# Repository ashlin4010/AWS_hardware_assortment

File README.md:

# AWS Hardware Assortment
This is a assortment of pcbs made for a Convergent Technologies AWS.
These designs may contain faults or errors that could destroy or damage the themselves or the AWS.
USE AT YOUR OWN RISK

## Bill of Materials
At this stage I have not create a bill of materials, if and when I make updates  to the designs I will try to improve the documentation.

## USB To AWS Cluster Interface
The AWS communicates with two differential pairs, one for clock and one for data.
This board uses the
[Adafruit FT232H Breakout](https://www.adafruit.com/product/2264) combined with differential drivers/receivers to communicate with the cluster network.
It includes some leds controllable from the FT232H and overvoltage protection via a zener.
Note: This adaptor unlike the AWS is not able to transmit and receive to its self.

## CPU Interface Board
This is effectively a breakout board that allows an Turbo CPU board to interface with peripheralsand and receive power
inplace of the original AWS motherboard. It has the following functions: cluster connectors, keyboard connector,
speaker breakout and volume, power LED, reset button and LED, video interface connector, and power input.

## Composite Adapter (Untested)

The Composite Adapter is an attempts to convert the AWSs ttl video to composite. The adapter has been built to be modular,
one part contains a power supply circuit and differential line receiver.
The other part contains the circuitry that produces the sync signal and is responsible for combining everything into composite.
At this stage this adapter has not been testred and most of the resistor values are guesses hence the potentiometers.
Note: In order to create an NTSC compatible signal the AWS horizontal scan frequency needs to be decreased. This can be done via an external
clock at the J3 connector or Video Debug PCB (Pixel Clock of 14.1606MHz ≈ 15.734kHz horizontal scan).

## Video Debug Borad
The Video Debug Borad has to functions, provieds an external video clock and LED indicators for the character ROM.
The Video Debug Board is able to provide a small amount of insight into what the CRT controller is doing.
But for the most part is more decorative than functional.

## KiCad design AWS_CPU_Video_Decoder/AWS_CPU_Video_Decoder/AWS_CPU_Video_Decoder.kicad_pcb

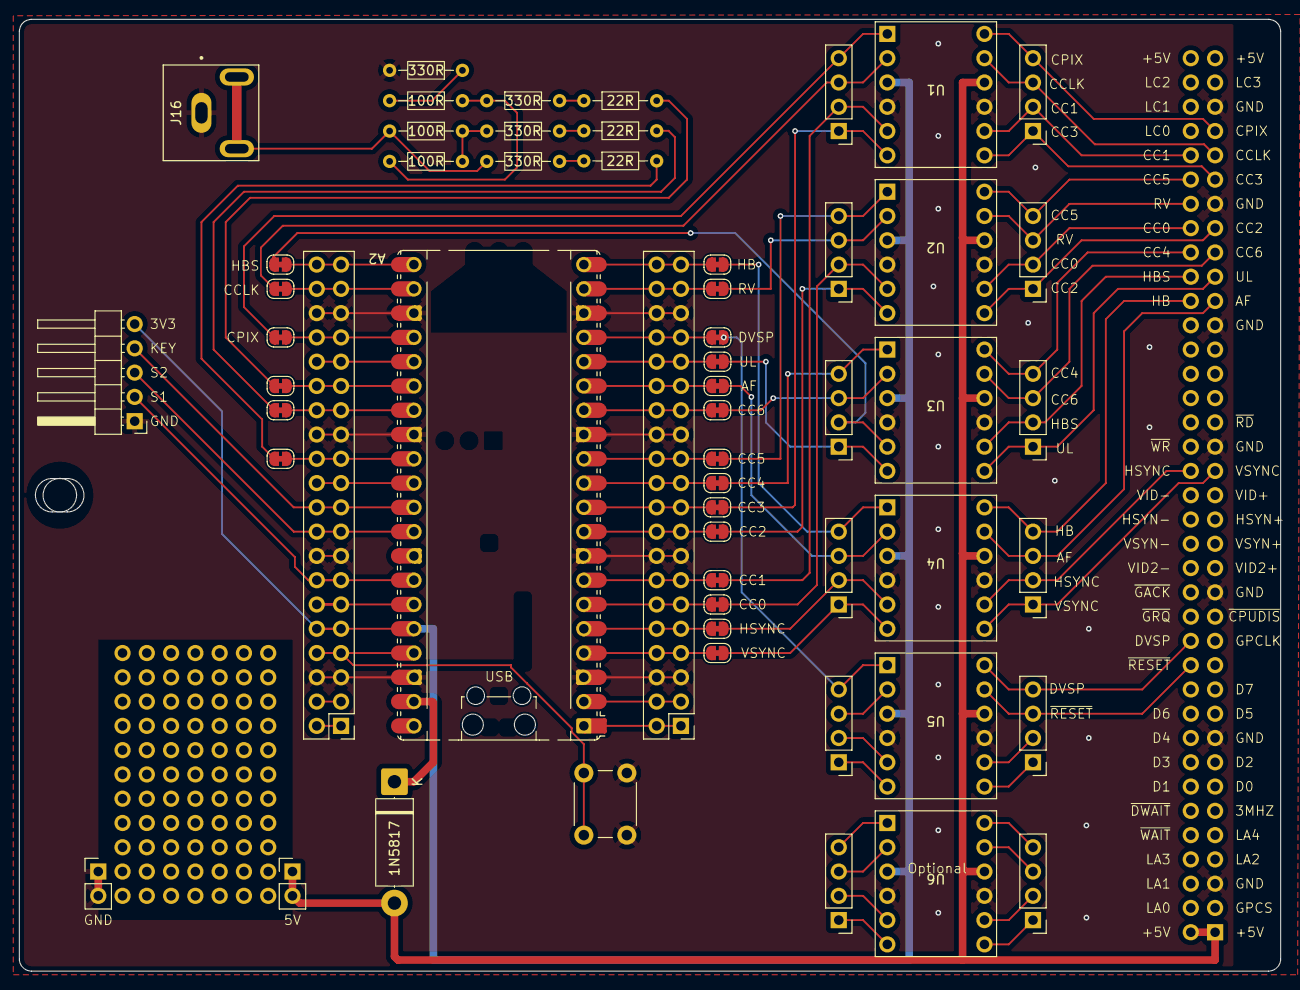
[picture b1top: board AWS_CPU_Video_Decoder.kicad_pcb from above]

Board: 2 copper layers, 132.0 x 99.6 mm, 59 parts (1 on the bottom side), 79 nets.

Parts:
A2: RaspberryPi_Pico; RaspberryPi_Pico_Common_Unspecified
D1: 1N5817; D_5W_P12.70mm_Horizontal
H1: MountingHole; MountingHole_3.5mm
J1, J5: Conn_02x20_Odd_Even; PinHeader_2x20_P2.54mm_Vertical
J2, J4, J6, J7, J8, J9, J10, J11, J12, J13, J14, J15: Conn_01x04_Pin; PinHeader_1x04_P2.54mm_Vertical
J3: Video; PinSocket_2x37_P2.54mm_Vertical
J16: Video; SWITCHCRAFT_PJRAN1X1U04X
J18, J19: Conn_01x02_Pin; PinHeader_1x02_P2.54mm_Vertical
J20: Encoder; PinHeader_1x05_P2.54mm_Horizontal
JP1, JP2, JP3, JP4, JP5, JP6, JP7, JP8, JP9, JP10, JP11, JP12, JP13, JP14, JP15, JP16, JP17, JP19, JP20, JP21: Jumper_2_Small_Bridged; SolderJumper-2_P1.3mm_Bridged_RoundedPad1.0x1.5mm
R1, R2, R3: 22R; R_Axial_DIN0204_L3.6mm_D1.6mm_P7.62mm_Horizontal
R4, R5, R6, R10: 330R; R_Axial_DIN0204_L3.6mm_D1.6mm_P7.62mm_Horizontal
R7, R8, R9: 100R; R_Axial_DIN0204_L3.6mm_D1.6mm_P7.62mm_Horizontal
SW1: Reset; SW_PUSH_6mm
U1, U2, U3, U4, U5, U6: level_shifter

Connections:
+3V3: A2.36 (3V3), J1.9, J1.10, J20.5, U1.3 (LV), U2.3 (LV), U3.3 (LV), U4.3 (LV), U5.3 (LV), U6.3 (LV)
+5V: D1.2 (A), J3.1, J3.2, J18.1, J18.2, U1.10 (HV), U2.10 (HV), U3.10 (HV), U4.10 (HV), U5.10 (HV), U6.10 (HV)
AF: J3.53, J15.3, U4.11 (HV2)
AF_LV: J7.3, JP10.1 (A), U4.2 (LV2)
CC0: J3.60, J12.2, U2.8 (HV3)
CC0_LV: J4.2, JP3.1 (A), U2.5 (LV3)
CC1: J3.66, J10.2, U1.8 (HV3)
CC1_LV: J2.2, JP4.1 (A), U1.5 (LV3)
CC2: J3.59, J12.1, U2.7 (HV4)
CC2_LV: J4.1, JP5.1 (A), U2.6 (LV4)
CC3: J3.63, J10.1, U1.7 (HV4)
CC3_LV: J2.1, JP6.1 (A), U1.6 (LV4)
CC4: J3.58, J14.4, U3.12 (HV1)
CC4_LV: J6.4, JP7.1 (A), U3.1 (LV1)
CC5: J3.64, J12.4, U2.12 (HV1)
CC5_LV: J4.4, JP8.1 (A), U2.1 (LV1)
CC6: J3.57, J14.3, U3.11 (HV2)
CC6_LV: J6.3, JP9.1 (A), U3.2 (LV2)
CCLK: J3.65, J10.3, U1.11 (HV2)
CCLK_LV: J2.3, JP15.2 (B), U1.2 (LV2)
CPIX: J3.67, J10.4, U1.12 (HV1)
CPIX_LV: J2.4, JP17.2 (B), U1.1 (LV1)
DAC0: A2.26 (GPIO20), J1.29, J1.30, JP21.2 (B)
DAC1: A2.27 (GPIO21), J1.27, J1.28, JP20.2 (B)
DAC2: A2.29 (GPIO22), J1.23, J1.24, JP19.2 (B)
DVSP: J3.26, J13.4, U5.12 (HV1)
DVSP_LV: J8.4, JP12.1 (A), U5.1 (LV1)
GND: A2.3 (GND), A2.8 (GND), A2.13 (GND), A2.18 (GND), A2.23 (GND), A2.28 (GND), A2.38 (GND), J1.5, J1.6, J1.15, J1.16, J1.25, J1.26, J1.35, J1.36, J3.5, J3.17, J3.29, J3.41, J3.51, J3.61, J3.69, J5.5, J5.6, J5.15, J5.16, J5.25, J5.26, J5.35, J5.36, J16.2 (Ext), J19.1, J19.2, J20.1, R10.2, SW1.2, U1.4 (GND), U1.9 (GND), U2.4 (GND), U2.9 (GND), U3.4 (GND), U3.9 (GND), U4.4 (GND), U4.9 (GND), U5.4 (GND), U5.9 (GND), U6.4 (GND), U6.9 (GND)
GPIO0: A2.1 (GPIO0), J5.1, J5.2
GPIO1: A2.2 (GPIO1), J5.3, J5.4
GPIO2: A2.4 (GPIO2), J5.7, J5.8, JP1.2 (B)
GPIO3: A2.5 (GPIO3), J5.9, J5.10, JP2.2 (B)
GPIO4: A2.6 (GPIO4), J5.11, J5.12, JP3.2 (B)
GPIO5: A2.7 (GPIO5), J5.13, J5.14, JP4.2 (B)
GPIO6: A2.9 (GPIO6), J5.17, J5.18, JP5.2 (B)
GPIO7: A2.10 (GPIO7), J5.19, J5.20, JP6.2 (B)
GPIO8: A2.11 (GPIO8), J5.21, J5.22, JP7.2 (B)
GPIO9: A2.12 (GPIO9), J5.23, J5.24, JP8.2 (B)
GPIO10: A2.14 (GPIO10), J5.27, J5.28, JP9.2 (B)
GPIO11: A2.15 (GPIO11), J5.29, J5.30, JP10.2 (B)
GPIO12: A2.16 (GPIO12), J5.31, J5.32, JP11.2 (B)
GPIO13: A2.17 (GPIO13), J5.33, J5.34, JP12.2 (B)
GPIO14: A2.19 (GPIO14), J5.37, J5.38, JP13.2 (B)
GPIO15: A2.20 (GPIO15), J5.39, J5.40, JP14.2 (B)
GPIO16: A2.21 (GPIO16), J1.39, J1.40, JP16.1 (A)
GPIO17: A2.22 (GPIO17), J1.37, J1.38, JP15.1 (A)
GPIO18: A2.24 (GPIO18), J1.33, J1.34, JP17.1 (A)
GPIO19: A2.25 (GPIO19), J1.31, J1.32
GPIO26: A2.31 (GPIO26_ADC0), J1.19, J1.20, J20.4
GPIO27: A2.32 (GPIO27_ADC1), J1.17, J1.18, J20.3
GPIO28: A2.34 (GPIO28_ADC2), J1.13, J1.14, J20.2
HB: J3.54, J15.4, U4.12 (HV1)
HBS: J3.56, J14.2, U3.8 (HV3)
HBS_LV: J6.2, JP16.2 (B), U3.5 (LV3)
HB_LV: J7.4, JP14.1 (A), U4.1 (LV1)
HSYNC: J3.40, J15.2, U4.8 (HV3)
HSYNC_LV: J7.2, JP2.1 (A), U4.5 (LV3)
unnamed: A2.39 (VSYS), D1.1 (K)
unnamed: J16.1 (In), R6.1, R8.1
unnamed: JP19.1 (A), R3.2
unnamed: JP20.1 (A), R2.2
unnamed: JP21.1 (A), R1.2
unnamed: R1.1, R4.2
unnamed: R2.1, R5.2
unnamed: R3.1, R6.2
unnamed: R4.1, R7.1, R9.2
unnamed: R5.1, R8.2, R9.1
unnamed: R7.2, R10.1
P_RESET: A2.37 (3V3_EN), J1.7, J1.8, SW1.1
RUN: A2.30 (RUN), J1.21, J1.22
RV: J3.62, J12.3, U2.11 (HV2)
RV_LV: J4.3, JP13.1 (A), U2.2 (LV2)
UL: J3.55, J14.1, U3.7 (HV4)
UL_LV: J6.1, JP11.1 (A), U3.6 (LV4)
VREF: A2.35 (ADC_VREF), J1.11, J1.12
VSYNC: J3.39, J15.1, U4.7 (HV4)
VSYNC_LV: J7.1, JP1.1 (A), U4.6 (LV4)
~RESET_LV: J8.3, U5.2 (LV2)
~RESET: J3.24, J13.3, U5.11 (HV2)

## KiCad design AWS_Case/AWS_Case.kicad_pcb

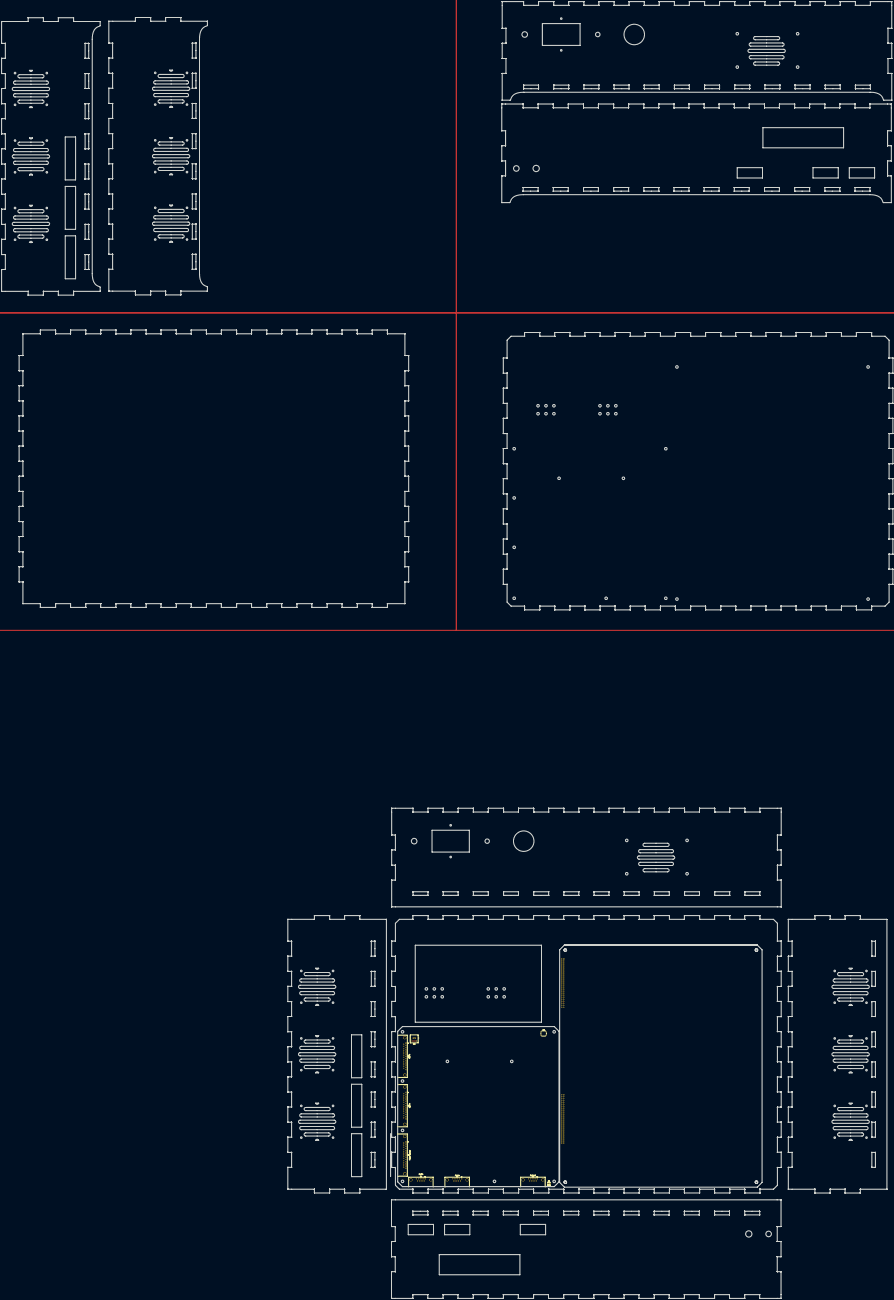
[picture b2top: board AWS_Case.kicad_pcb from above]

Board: 2 copper layers, 1122.7 x 1633.6 mm, 9 parts (0 on the bottom side), 6 nets, no tracks yet.

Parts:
D1: Power; LED_D3.0mm
J3, J4: Cluster; DSUB-9_Socket_Horizontal_P2.77x2.84mm_EdgePinOffset7.70mm_H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
J7: Keyboard; DSUB-9_Socket_Horizontal_P2.77x2.84mm_EdgePinOffset7.70mm_H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
J8: Printer Interface; DSUB-25_Pins_Horizontal_P2.77x2.84mm_EdgePinOffset7.70mm_Ho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
J9: UART A; DSUB-25_Pins_Horizontal_P2.77x2.84mm_EdgePinOffset7.70mm_Ho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
J10: UART B; DSUB-25_Pins_Horizontal_P2.77x2.84mm_EdgePinOffset7.70mm_Ho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
J12: Video; SWITCHCRAFT_PJRAN1X1U04X
SW1: Reset; SW_PUSH_6mm

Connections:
+5V: J7.6, J7.7
CPU_RXCA+: J3.6, J4.6
CPU_RXCA-: J3.7, J4.7
CPU_RXDA+: J3.8, J4.8
CPU_RXDA-: J3.9, J4.9
GND: D1.1 (K), J3.1, J3.2, J3.3, J3.4, J3.5, J4.1, J4.2, J4.3, J4.4, J4.5, J7.2, J7.4, J7.8, J7.9, J8.9, J8.10, J8.11, J8.12, J8.13, J8.15, J8.23, J8.24, J8.25, J9.1, J9.7, J9.9, J10.1, J10.7, J10.9, J12.2 (Ext), SW1.2

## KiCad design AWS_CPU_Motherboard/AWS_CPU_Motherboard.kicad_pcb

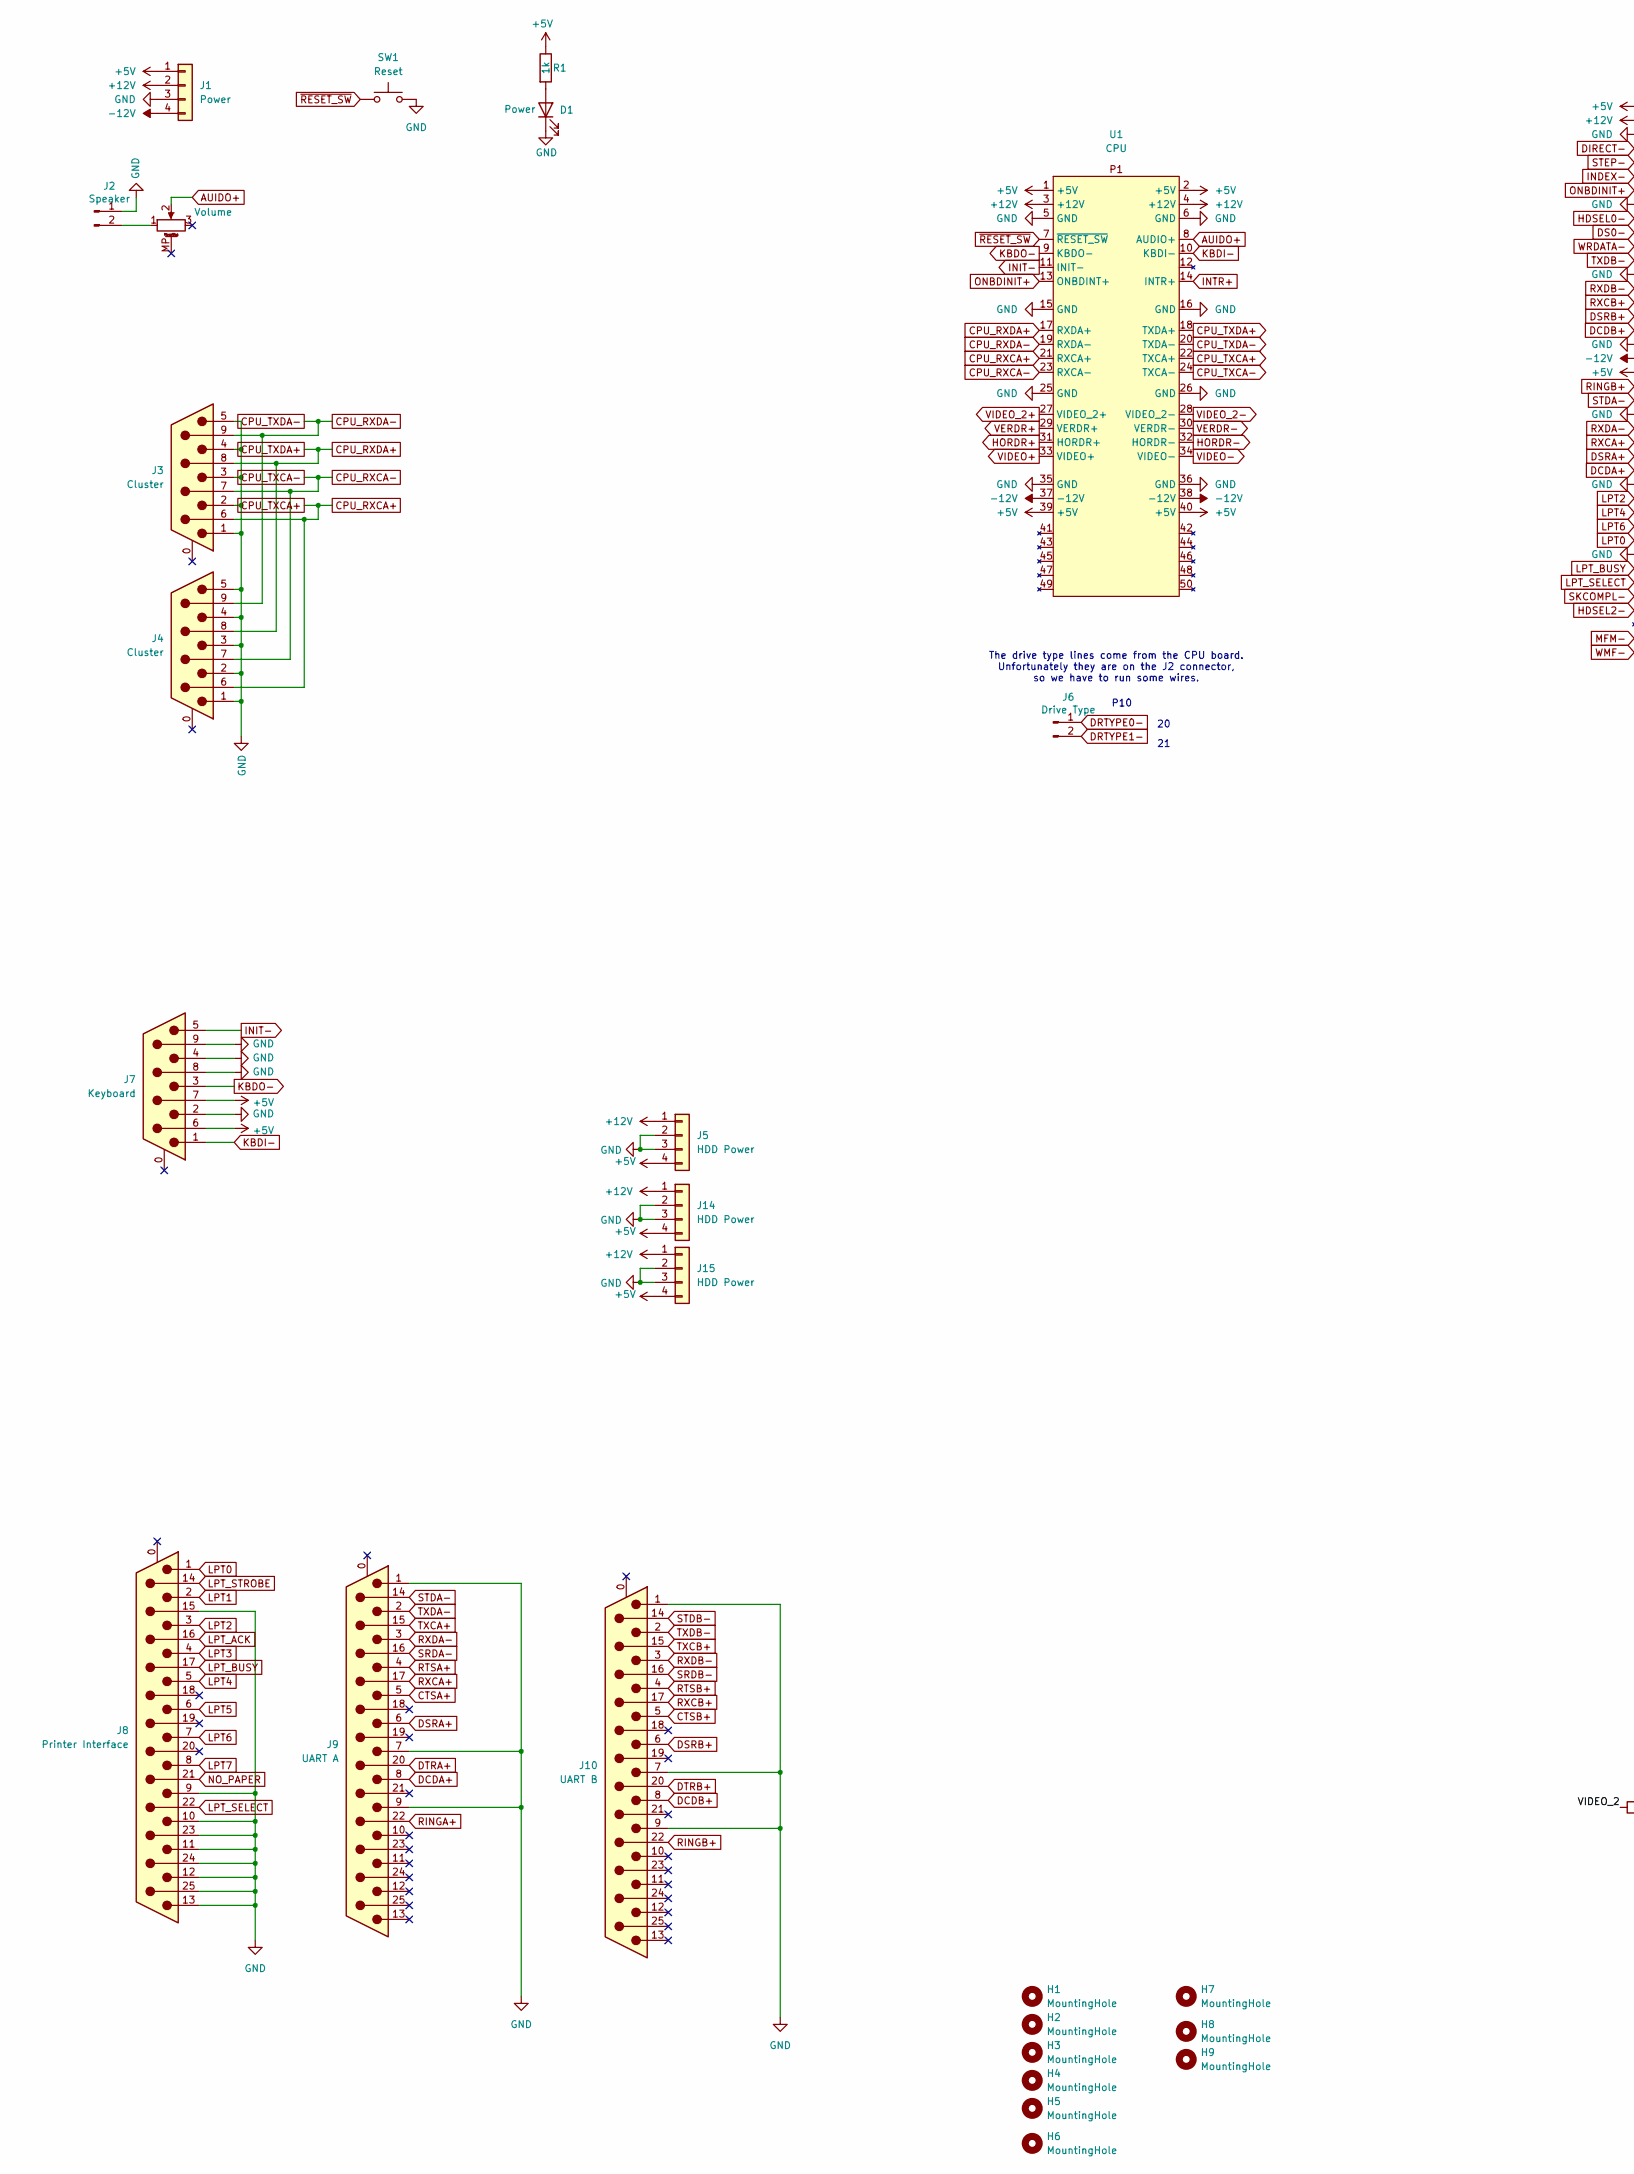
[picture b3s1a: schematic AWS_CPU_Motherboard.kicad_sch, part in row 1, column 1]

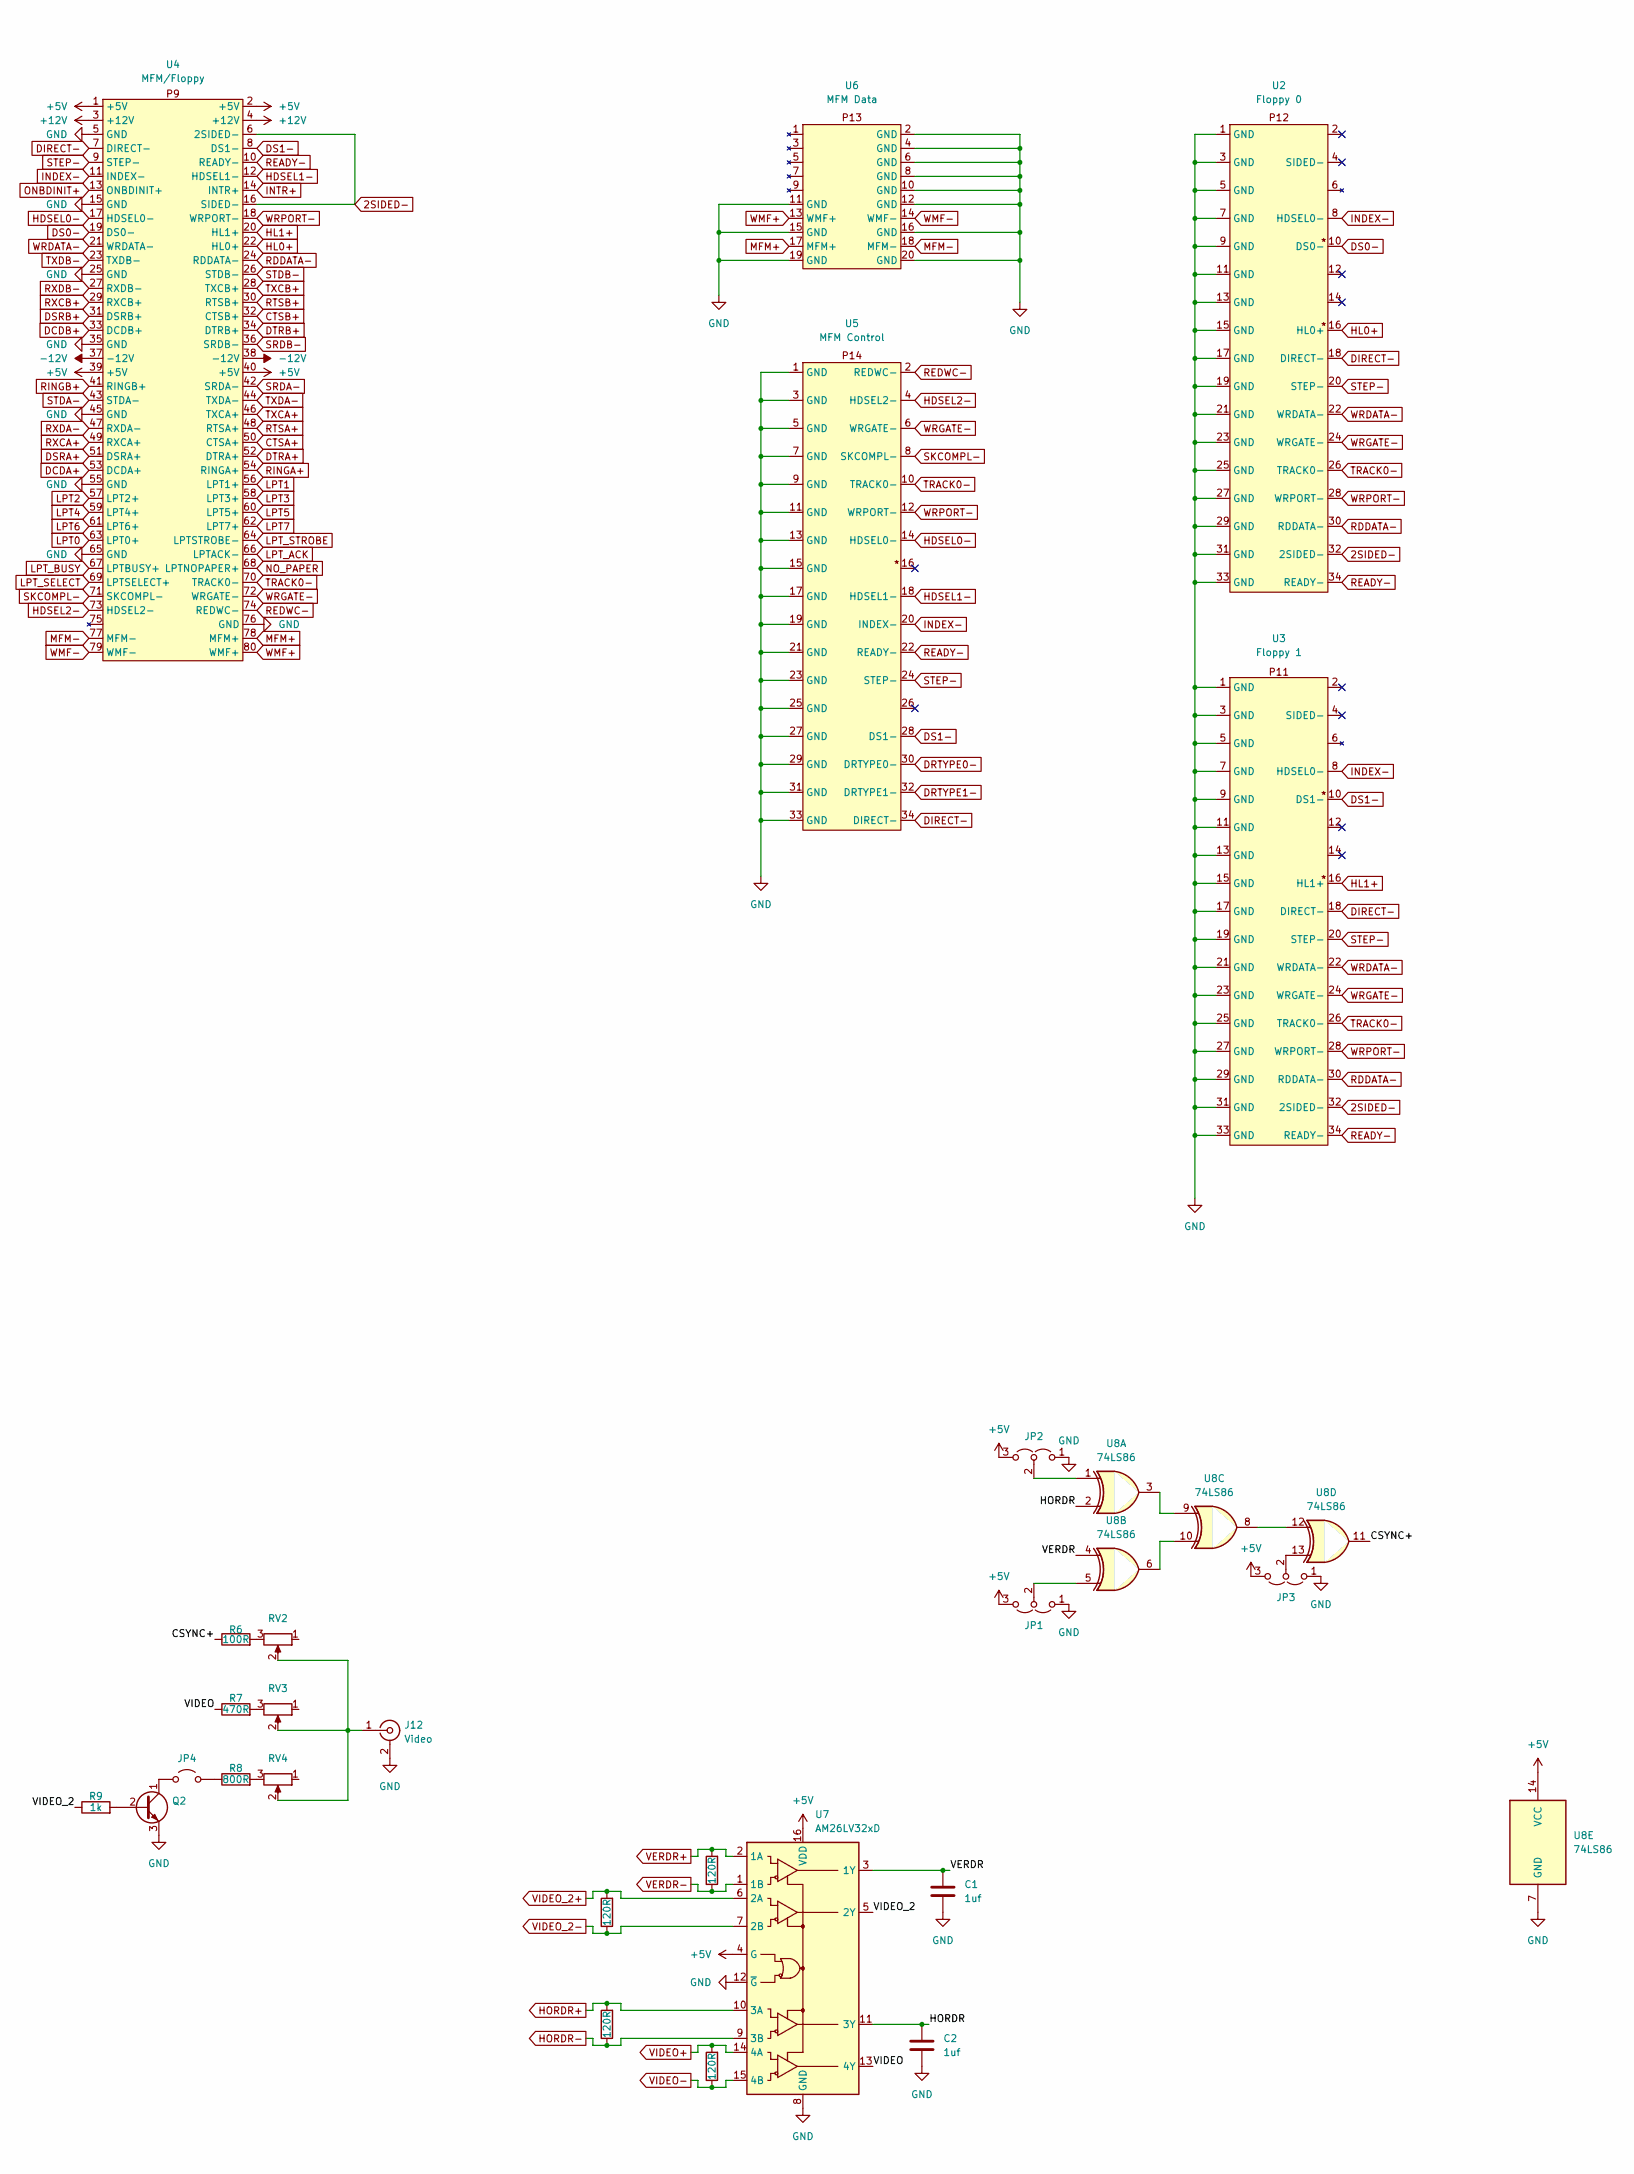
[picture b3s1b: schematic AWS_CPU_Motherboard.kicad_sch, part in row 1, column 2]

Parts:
C1, C2: 1uf; C_Disc_D3.0mm_W1.6mm_P2.50mm
D1: Power; LED_D3.0mm
H1, H2, H3, H4, H5, H6, H7, H8, H9: MountingHole; MountingHole_3.2mm_M3
J1: Power; TerminalBlock_Dinkle_DT-55-B01X-04_P10.00mm
J2: Speaker; PinHeader_1x02_P2.54mm_Vertical
J3, J4: Cluster; DSUB-9_Socket_Horizontal_P2.77x2.84mm_EdgePinOffset7.70mm_H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
J5, J14, J15: HDD Power; TE_MATE-N-LOK_350211-1_1x04_P5.08mm_Vertical
J6: Drive Type; PinHeader_1x02_P2.54mm_Vertical
J7: Keyboard; DSUB-9_Socket_Horizontal_P2.77x2.84mm_EdgePinOffset7.70mm_H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
J8: Printer Interface; DSUB-25_Pins_Horizontal_P2.77x2.84mm_EdgePinOffset7.70mm_Ho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
J9: UART A; DSUB-25_Pins_Horizontal_P2.77x2.84mm_EdgePinOffset7.70mm_Ho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
J10: UART B; DSUB-25_Pins_Horizontal_P2.77x2.84mm_EdgePinOffset7.70mm_Ho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
J12: Video; SWITCHCRAFT_PJRAN1X1U04X
JP1, JP2, JP3: Jumper_3_Open; PinHeader_1x03_P2.54mm_Vertical
JP4: Enable Half Bright; PinHeader_1x02_P2.54mm_Vertical
Q2: Q_NPN_CBE; TO-92
R1, R9: 1k; R_Axial_DIN0204_L3.6mm_D1.6mm_P7.62mm_Horizontal
R2, R3, R4, R5: 120R; R_Axial_DIN0204_L3.6mm_D1.6mm_P7.62mm_Horizontal
R6: 100R; R_Axial_DIN0204_L3.6mm_D1.6mm_P7.62mm_Horizontal
R7: 470R; R_Axial_DIN0204_L3.6mm_D1.6mm_P7.62mm_Horizontal
R8: 800R; R_Axial_DIN0204_L3.6mm_D1.6mm_P7.62mm_Horizontal
RV1: Volume; Potentiometer_Bourns_PTV09A-1_Single_Vertical
RV2: CSYNC+; Potentiometer_Piher_PT-10-V10_Vertical
RV3: VIDEO; Potentiometer_Piher_PT-10-V10_Vertical
RV4: Half; Potentiometer_Piher_PT-10-V10_Vertical
SW1: Reset; SW_PUSH_6mm
U1: CPU; IDC-Header_2x25_P2.54mm_Vertical_Reversed
U2: Floppy 0; IDC-Header_2x17_P2.54mm_Vertical
U3: Floppy 1; IDC-Header_2x17_P2.54mm_Vertical
U4: MFM/Floppy; PinHeader_2x40_P2.54mm_Horizontal_Reversed
U5: MFM Control; IDC-Header_2x17_P2.54mm_Vertical
U6: MFM Data; IDC-Header_2x10_P2.54mm_Vertical
U7: AM26LV32xD; DIP-16_W7.62mm_LongPads
U8: 74LS86; DIP-14_W7.62mm_LongPads

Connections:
2SIDED-: U2.32 (2SIDED-), U3.32 (2SIDED-), U4.6 (2SIDED-), U4.16 (SIDED-)
+5V: J1.1, J5.4, J7.6, J7.7, J14.4, J15.4, JP1.3 (B), JP2.3 (B), JP3.3 (B), R1.1, U1.1 (+5V), U1.2 (+5V), U1.39 (+5V), U1.40 (+5V), U4.1 (+5V), U4.2 (+5V), U4.39 (+5V), U4.40 (+5V), U7.4 (G), U7.16 (VDD), U8.14 (VCC)
+12V: J1.2, J5.1, J14.1, J15.1, U1.3 (+12V), U1.4 (+12V), U4.3 (+12V), U4.4 (+12V)
-12V: J1.4, U1.37 (-12V), U1.38 (-12V), U4.37 (-12V), U4.38 (-12V)
/CSYNC+: R6.1, U8.11
/HORDR: C2.1, U7.11 (3Y), U8.2
/VERDR: C1.1, U7.3 (1Y), U8.4
/VIDEO: R7.1, U7.13 (4Y)
/VIDEO_2: R9.1, U7.5 (2Y)
AUIDO+: RV1.2, U1.8 (AUDIO+)
CPU_RXCA+: J3.6, J4.6, U1.21 (RXCA+), U1.22 (TXCA+)
CPU_RXCA-: J3.7, J4.7, U1.23 (RXCA-), U1.24 (TXCA-)
CPU_RXDA+: J3.8, J4.8, U1.17 (RXDA+), U1.18 (TXDA+)
CPU_RXDA-: J3.9, J4.9, U1.19 (RXDA-), U1.20 (TXDA-)
CTSA+: J9.5, U4.50 (CTSA+)
CTSB+: J10.5, U4.32 (CTSB+)
DCDA+: J9.8, U4.53 (DCDA+)
DCDB+: J10.8, U4.33 (DCDB+)
DIRECT-: U2.18 (DIRECT-), U3.18 (DIRECT-), U4.7 (DIRECT-), U5.34 (DIRECT-)
DRTYPE0-: J6.1, U5.30 (DRTYPE0-)
DRTYPE1-: J6.2, U5.32 (DRTYPE1-)
DS0-: U2.10 (DS0-), U4.19 (DS0-)
DS1-: U3.10 (DS1-), U4.8 (DS1-), U5.28 (DS1-)
DSRA+: J9.6, U4.51 (DSRA+)
DSRB+: J10.6, U4.31 (DSRB+)
DTRA+: J9.20, U4.52 (DTRA+)
DTRB+: J10.20, U4.34 (DTRB+)
GND: C1.2, C2.2, D1.1 (K), J1.3, J2.1, J3.1, J3.2, J3.3, J3.4, J3.5, J4.1, J4.2, J4.3, J4.4, J4.5, J5.2, J5.3, J7.2, J7.4, J7.8, J7.9, J8.9, J8.10, J8.11, J8.12, J8.13, J8.15, J8.23, J8.24, J8.25, J9.1, J9.7, J9.9, J10.1, J10.7, J10.9, J12.2 (Ext), J14.2, J14.3, J15.2, J15.3, JP1.1 (A), JP2.1 (A), JP3.1 (A), Q2.3 (E), SW1.2, U1.5 (GND), U1.6 (GND), U1.15 (GND), U1.16 (GND), U1.25 (GND), U1.26 (GND), U1.35 (GND), U1.36 (GND), U2.1 (GND), U2.3 (GND), U2.5 (GND), U2.7 (GND), U2.9 (GND), U2.11 (GND), U2.13 (GND), U2.15 (GND), U2.17 (GND), U2.19 (GND), U2.21 (GND), U2.23 (GND), U2.25 (GND), U2.27 (GND), U2.29 (GND), U2.31 (GND), U2.33 (GND), U3.1 (GND), U3.3 (GND), U3.5 (GND), U3.7 (GND), U3.9 (GND), U3.11 (GND), U3.13 (GND), U3.15 (GND), U3.17 (GND), U3.19 (GND), U3.21 (GND), U3.23 (GND), U3.25 (GND), U3.27 (GND), U3.29 (GND), U3.31 (GND), U3.33 (GND), U4.5 (GND), U4.15 (GND), U4.25 (GND), U4.35 (GND), U4.45 (GND), U4.55 (GND), U4.65 (GND), U4.76 (GND), U5.1 (GND), U5.3 (GND), U5.5 (GND), U5.7 (GND), U5.9 (GND), U5.11 (GND), U5.13 (GND), U5.15 (GND), U5.17 (GND), U5.19 (GND), U5.21 (GND), U5.23 (GND), U5.25 (GND), U5.27 (GND), U5.29 (GND), U5.31 (GND), U5.33 (GND), U6.2 (GND), U6.4 (GND), U6.6 (GND), U6.8 (GND), U6.10 (GND), U6.11 (GND), U6.12 (GND), U6.15 (GND), U6.16 (GND), U6.19 (GND), U6.20 (GND), U7.8 (GND), U7.12 (~G), U8.7 (GND)
HDSEL0-: U4.17 (HDSEL0-), U5.14 (HDSEL0-)
HDSEL1-: U4.12 (HDSEL1-), U5.18 (HDSEL1-)
HDSEL2-: U4.73 (HDSEL2-), U5.4 (HDSEL2-)
HL0+: U2.16 (HL0+), U4.22 (HL0+)
HL1+: U3.16 (HL1+), U4.20 (HL1+)
HORDR+: R5.2, U1.31 (HORDR+), U7.10 (3A)
HORDR-: R5.1, U1.32 (HORDR-), U7.9 (3B)
INDEX-: U2.8 (HDSEL0-), U3.8 (HDSEL0-), U4.11 (INDEX-), U5.20 (INDEX-)
INIT-: J7.5, U1.11 (INIT-)
INTR+: U1.14 (INTR+), U4.14 (INTR+)
KBDI-: J7.1, U1.10 (KBDI-)
KBDO-: J7.3, U1.9 (KBDO-)
LPT0: J8.1, U4.63 (LPT0+)
LPT1: J8.2, U4.56 (LPT1+)
LPT2: J8.3, U4.57 (LPT2+)
LPT3: J8.4, U4.58 (LPT3+)
LPT4: J8.5, U4.59 (LPT4+)
LPT5: J8.6, U4.60 (LPT5+)
LPT6: J8.7, U4.61 (LPT6+)
LPT7: J8.8, U4.62 (LPT7+)
LPT_ACK: J8.16, U4.66 (LPTACK-)
LPT_BUSY: J8.17, U4.67 (LPTBUSY+)
LPT_SELECT: J8.22, U4.69 (LPTSELECT+)
LPT_STROBE: J8.14, U4.64 (LPTSTROBE-)
MFM+: U4.78 (MFM+), U6.17 (MFM+)
MFM-: U4.77 (MFM-), U6.18 (MFM-)
NO_PAPER: J8.21, U4.68 (LPTNOPAPER+)
unnamed: D1.2 (A), R1.2
unnamed: J2.2, RV1.1
unnamed: J12.1 (In), RV2.2, RV3.2, RV4.2
unnamed: JP1.2 (C), U8.5
unnamed: JP2.2 (C), U8.1
unnamed: JP3.2 (C), U8.13
unnamed: JP4.1 (A), Q2.1 (C)
unnamed: JP4.2 (B), R8.1
unnamed: Q2.2 (B), R9.2
unnamed: R6.2, RV2.3
unnamed: R7.2, RV3.3
unnamed: R8.2, RV4.3
unnamed: U8.3, U8.9
unnamed: U8.6, U8.10
unnamed: U8.8, U8.12
ONBDINIT+: U1.13 (ONBDINT+), U4.13 (ONBDINIT+)
RDDATA-: U2.30 (RDDATA-), U3.30 (RDDATA-), U4.24 (RDDATA-)
READY-: U2.34 (READY-), U3.34 (READY-), U4.10 (READY-), U5.22 (READY-)
REDWC-: U4.74 (REDWC-), U5.2 (REDWC-)
RINGA+: J9.22, U4.54 (RINGA+)
RINGB+: J10.22, U4.41 (RINGB+)
RTSA+: J9.4, U4.48 (RTSA+)
RTSB+: J10.4, U4.30 (RTSB+)
RXCA+: J9.17, U4.49 (RXCA+)
RXCB+: J10.17, U4.29 (RXCB+)
RXDA-: J9.3, U4.47 (RXDA-)
RXDB-: J10.3, U4.27 (RXDB-)
SKCOMPL-: U4.71 (SKCOMPL-), U5.8 (SKCOMPL-)
SRDA-: J9.16, U4.42 (SRDA-)
SRDB-: J10.16, U4.36 (SRDB-)
STDA-: J9.14, U4.43 (STDA-)
STDB-: J10.14, U4.26 (STDB-)
STEP-: U2.20 (STEP-), U3.20 (STEP-), U4.9 (STEP-), U5.24 (STEP-)
TRACK0-: U2.26 (TRACK0-), U3.26 (TRACK0-), U4.70 (TRACK0-), U5.10 (TRACK0-)
TXCA+: J9.15, U4.46 (TXCA+)
TXCB+: J10.15, U4.28 (TXCB+)
TXDA-: J9.2, U4.44 (TXDA-)
TXDB-: J10.2, U4.23 (TXDB-)
VERDR+: R2.2, U1.29 (VERDR+), U7.2 (1A)
VERDR-: R2.1, U1.30 (VERDR-), U7.1 (1B)
VIDEO+: R3.2, U1.33 (VIDEO+), U7.14 (4A)
VIDEO-: R3.1, U1.34 (VIDEO-), U7.15 (4B)
VIDEO_2+: R4.2, U1.27 (VIDEO_2+), U7.6 (2A)
VIDEO_2-: R4.1, U1.28 (VIDEO_2-), U7.7 (2B)
WMF+: U4.80 (WMF+), U6.13 (WMF+)
WMF-: U4.79 (WMF-), U6.14 (WMF-)
WRDATA-: U2.22 (WRDATA-), U3.22 (WRDATA-), U4.21 (WRDATA-)
WRGATE-: U2.24 (WRGATE-), U3.24 (WRGATE-), U4.72 (WRGATE-), U5.6 (WRGATE-)
WRPORT-: U2.28 (WRPORT-), U3.28 (WRPORT-), U4.18 (WRPORT-), U5.12 (WRPORT-)
~RESET_SW: SW1.1, U1.7 (~RESET_SW)

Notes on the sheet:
The drive type lines come from the CPU board. Unfortunately they are on the J2 connector, so we have to run some wires.
P10

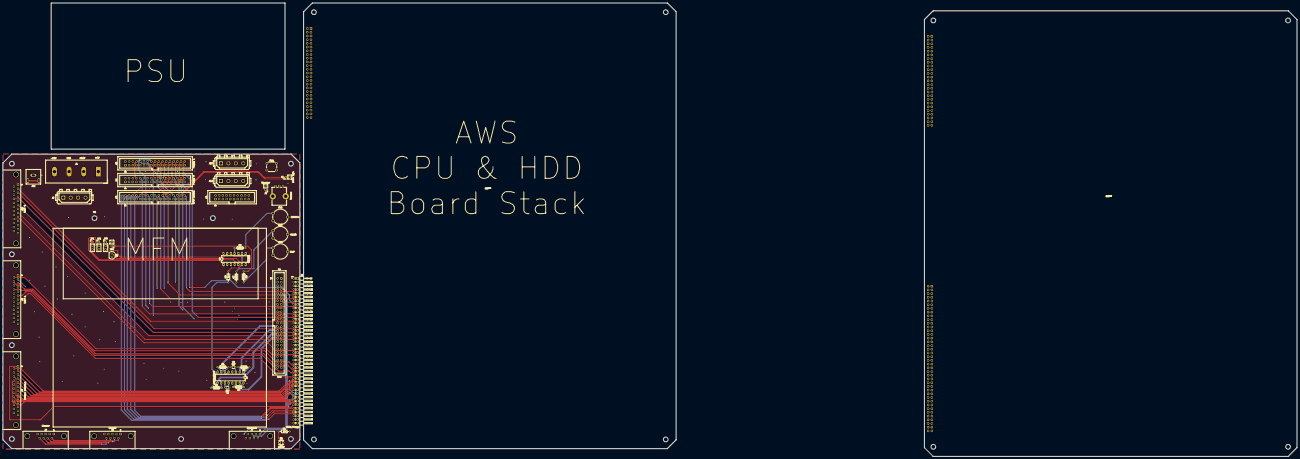
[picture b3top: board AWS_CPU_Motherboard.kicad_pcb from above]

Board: 4 copper layers, 885.7 x 310.3 mm, 52 parts (0 on the bottom side), 105 nets.

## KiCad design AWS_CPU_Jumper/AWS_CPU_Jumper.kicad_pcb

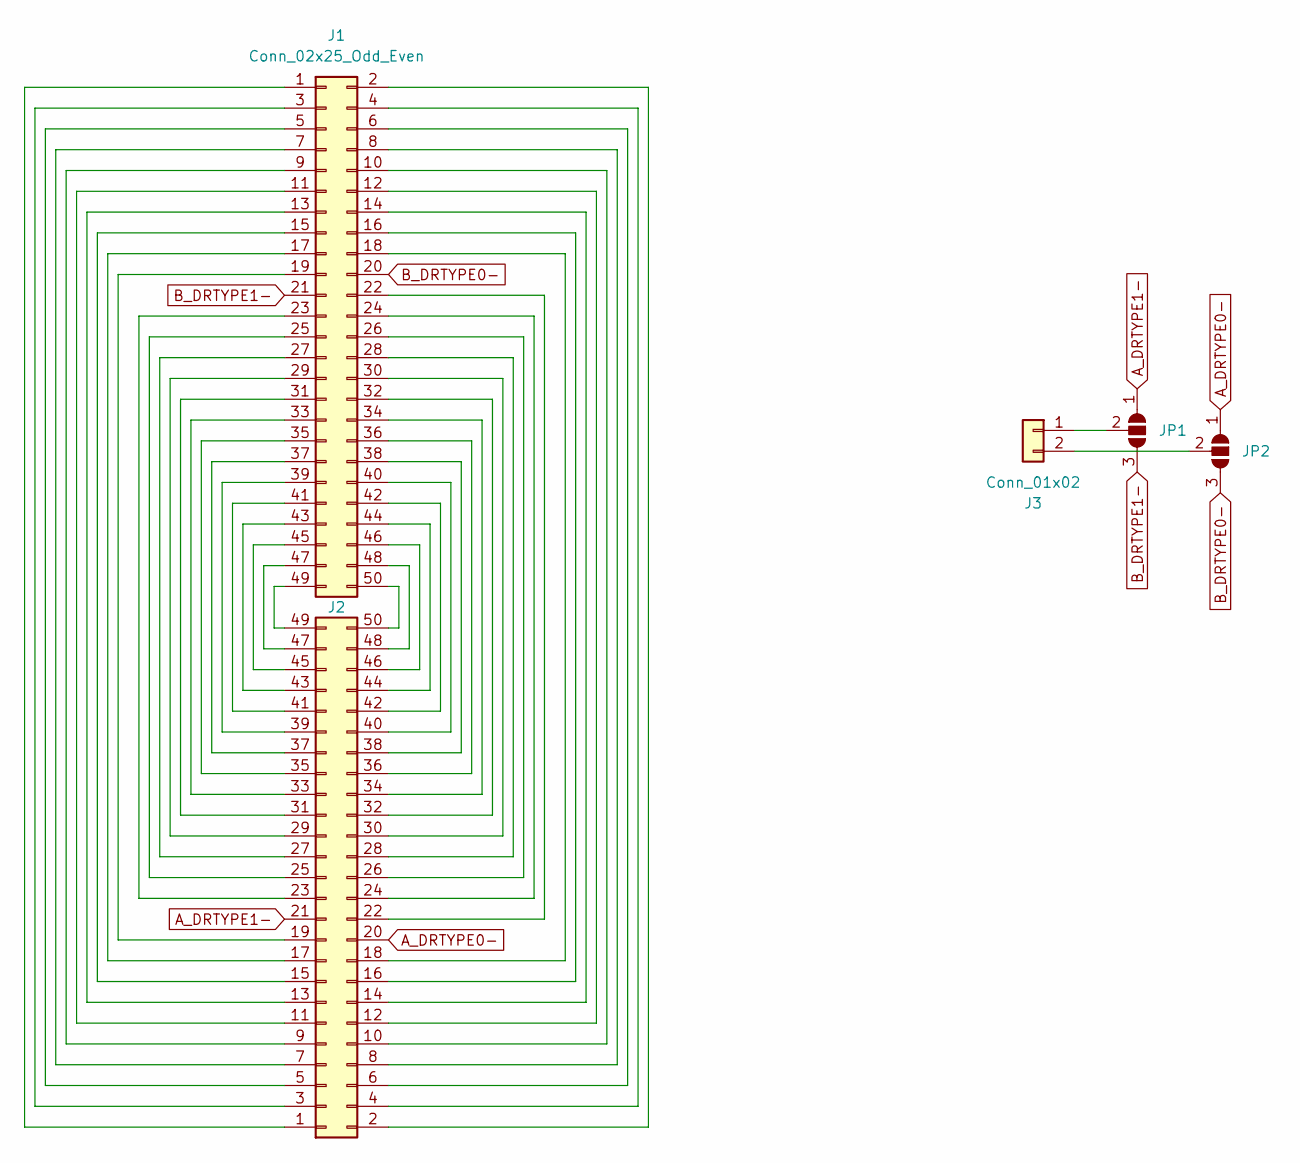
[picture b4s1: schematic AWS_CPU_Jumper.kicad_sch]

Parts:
J1, J2: Conn_02x25_Odd_Even; PinHeader_2x25_P2.54mm_Vertical
J3: Conn_01x02; PinHeader_1x02_P2.54mm_Vertical
JP1, JP2: SolderJumper_3_Open; SolderJumper-3_P1.3mm_Open_RoundedPad1.0x1.5mm

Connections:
A_DRTYPE0-: J2.20, JP2.1 (A)
A_DRTYPE1-: J2.21, JP1.1 (A)
B_DRTYPE0-: J1.20, JP2.3 (B)
B_DRTYPE1-: J1.21, JP1.3 (B)
unnamed: J1.1, J2.1
unnamed: J1.2, J2.2
unnamed: J1.3, J2.3
unnamed: J1.4, J2.4
unnamed: J1.5, J2.5
unnamed: J1.6, J2.6
unnamed: J1.7, J2.7
unnamed: J1.8, J2.8
unnamed: J1.9, J2.9
unnamed: J1.10, J2.10
unnamed: J1.11, J2.11
unnamed: J1.12, J2.12
unnamed: J1.13, J2.13
unnamed: J1.14, J2.14
unnamed: J1.15, J2.15
unnamed: J1.16, J2.16
unnamed: J1.17, J2.17
unnamed: J1.18, J2.18
unnamed: J1.19, J2.19
unnamed: J1.22, J2.22
unnamed: J1.23, J2.23
unnamed: J1.24, J2.24
unnamed: J1.25, J2.25
unnamed: J1.26, J2.26
unnamed: J1.27, J2.27
unnamed: J1.28, J2.28
unnamed: J1.29, J2.29
unnamed: J1.30, J2.30
unnamed: J1.31, J2.31
unnamed: J1.32, J2.32
unnamed: J1.33, J2.33
unnamed: J1.34, J2.34
unnamed: J1.35, J2.35
unnamed: J1.36, J2.36
unnamed: J1.37, J2.37
unnamed: J1.38, J2.38
unnamed: J1.39, J2.39
unnamed: J1.40, J2.40
unnamed: J1.41, J2.41
unnamed: J1.42, J2.42
unnamed: J1.43, J2.43
unnamed: J1.44, J2.44
unnamed: J1.45, J2.45
unnamed: J1.46, J2.46
unnamed: J1.47, J2.47
unnamed: J1.48, J2.48
unnamed: J1.49, J2.49
unnamed: J1.50, J2.50
unnamed: J3.1, JP1.2 (C)
unnamed: J3.2, JP2.2 (C)

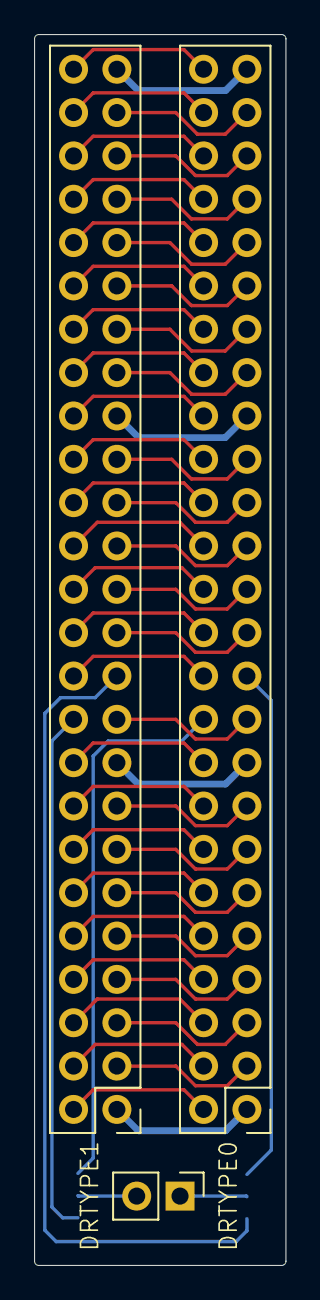
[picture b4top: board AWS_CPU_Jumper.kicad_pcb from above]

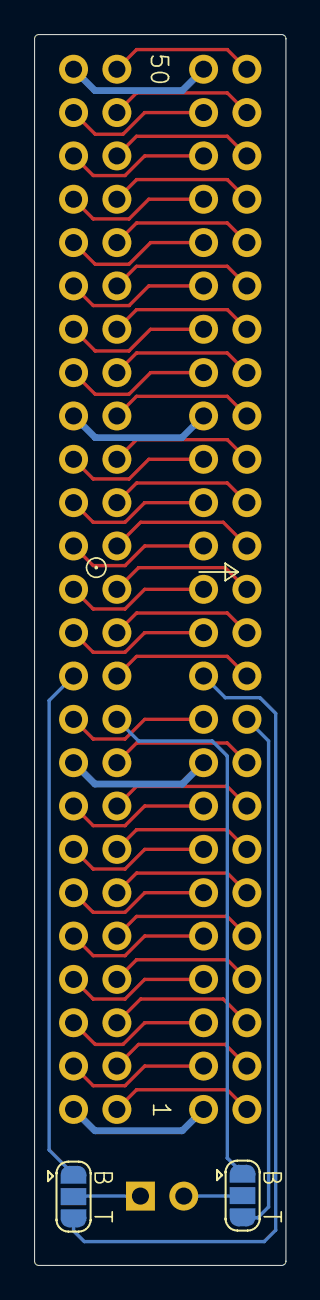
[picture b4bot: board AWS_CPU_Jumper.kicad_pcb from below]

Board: 2 copper layers, 14.7 x 72.1 mm, 5 parts (2 on the bottom side), 54 nets.
